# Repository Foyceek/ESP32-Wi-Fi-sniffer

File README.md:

# ESP32-Wi-Fi-sniffer
## Užitečné odkazy
- [ESP32 One overview](https://www.waveshare.com/wiki/ESP32_One)
- [Overleaf](https://www.overleaf.com/project)
- [VUT závěrečné práce](https://www.vut.cz/studenti/zav-prace)
- [IEEE Xplore](https://ieeexplore.ieee.org/Xplore/home.jsp)
- [How to install MicroPython on an ESP32 microcontroller](https://pythonforundergradengineers.com/how-to-install-micropython-on-an-esp32.html)
- [ESP-IDF course](https://github.com/tomas-fryza/esp-idf)
- [ESP-Arduino course](https://github.com/tomas-fryza/esp-arduino)
- [ESP-Micropython course](https://github.com/tomas-fryza/esp-micropython)
- [Probe request project](https://github.com/tomas-fryza/probe-request-project)
- [ESP32 Probe Sniffer-tbravenec](https://gitlab.com/tbravenec/esp32-probe-sniffer)
## Současný prototyp
[Zdrojový kód snifferu](https://github.com/Foyceek/ESP32-Wi-Fi-sniffer/tree/main/ESP-IDF/ESP32_Wi-Fi_SNIFFER)

[Zdrojový kód aplikace](https://github.com/Foyceek/ESP32-Wi-Fi-sniffer/blob/main/Probe_Request_Analysis_App/README.md)

Obě tlačítka mají každé 4 funkce:
- Krátký stisk (50-500ms)
- Střední stisk (500-1000ms)
- Dlouhý stisk (>1000ms)
- Dvojtý stisk

Časy se dají měnit, současné stisknutí obou tlačítek po dobu alespoň 2s zastaví aplikaci aby bylo možné bezpečně odpojit napájení.

### Funkce horního tlačítka

Procházení informací na OLED displeji

- Krátký stisk posun vpřed
- Střední stisk návrat na první záznam
- Dlouhý stisk přepínání mezi dobou vypnutí OLED při nečinnosti 5s, 30s nebo 1h
- Dvojitý stisk posun vzad

### Funkce dolního tlačítka

Uprava počtu záznamů na OLED displeji

- Krátký stisk +1 záznam
- Střední stisk obnovetní původního počtu záznamů
- Dlouhý stisk přepíná mezi zachytáváním probe requestů a spuštění webserveru s možností stažení sesbíraných dat.
- Dvojitý stisk -1 záznam

### Fotodokumentace

Příklad captive portálu po krátkém spuštění snifferu

## Závěrečná práce
- Název: Vývoj embedded zařízení pro monitorování a sběr Wi-Fi probe requestů
- Název anglicky: Development of embedded device for monitoring and collecting Wi-Fi probe requests
## Základní literární prameny
[1] BRAVENEC, T. ESP32 Probe Request Sniffer. Online. GitLab. Dostupné z: https://gitlab.com/tbravenec/esp32-probe-sniffer. [cit. 2024-05-27]
[2] RUSCA, R., SANSOLDO, F., CASETTI, C., GIACCONE, P. What WiFi Probe Requests can tell you, 2023 IEEE 20th Consumer Communications & Networking Conference (CCNC), Las Vegas, NV, USA, 2023, pp. 1086-1091, doi: 10.1109/CCNC51644.2023.10060447

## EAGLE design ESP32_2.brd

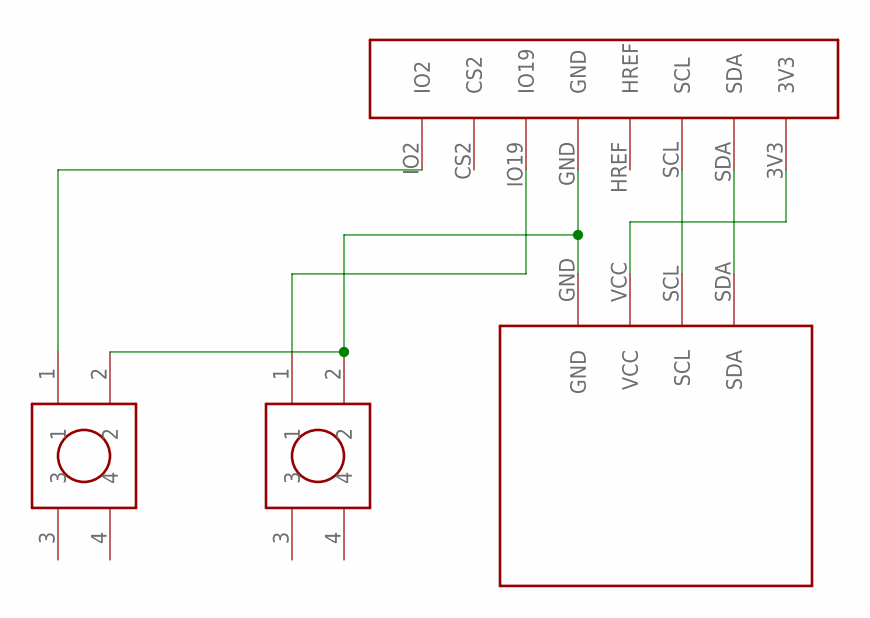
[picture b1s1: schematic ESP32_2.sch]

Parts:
U$1, U$2: TACT_BUTTON
U$3: OLED_0.96"
U$4: ESP32_1X8

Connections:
GND: U$1.2, U$2.2, U$3.GND, U$4.GND
IO2: U$1.1, U$4.IO2
IO19: U$2.1, U$4.IO19
SCL: U$3.SCL, U$4.SCL
SDA: U$3.SDA, U$4.SDA
VCC: U$3.VCC, U$4.3V3

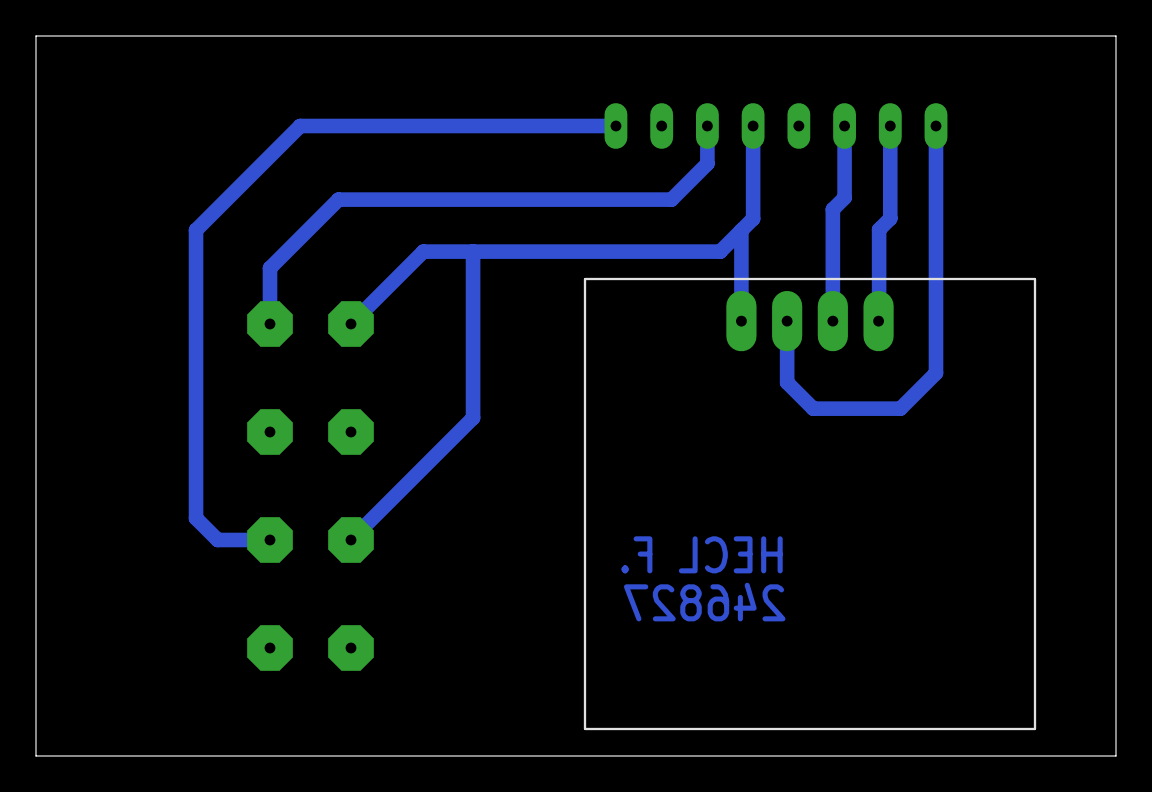
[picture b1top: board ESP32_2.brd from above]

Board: 2 copper layers, 60.0 x 40.0 mm, 4 parts (0 on the bottom side), 6 nets.

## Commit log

2024-11-04 Rename ESP-IDF/REDUCED_DATA.csv to ESP-IDF/test1/REDUCED_DATA.csv
2024-11-15 Create main
2024-11-17 Create Python
2024-11-17 Rename Analýza.md to README.md
2024-11-30 Rename ESP-IDF/radiotap_csv_pcap2/main.txt to ESP-IDF/radiotap_csv_pcap_2
